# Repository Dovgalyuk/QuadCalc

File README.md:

# QuadCalc
Arduino-based calculator displaying bin/oct/dec/hex versions of argument and result simultaneously

Schematic: https://github.com/Dovgalyuk/QuadCalc/blob/master/pcb-avr/pcb.pdf

## Flashing

Read low fuse bits into file low:

    sudo avrdude -p m2560 -c usbtiny -U lfuse:r:low:r

Write low fuse bits from file low. It should contain single FF byte:

    sudo avrdude -p m2560 -c usbtiny -U lfuse:w:low:r

Write high fuse bits from file high. It should contain single D8 byte:

    sudo avrdude -p m2560 -c usbtiny -U hfuse:w:high:r

Write the firmware image:

    sudo avrdude -p m2560 -c usbtiny -U flash:w:calc.ino.hex:i

# Links

* MK61 hardware emulator: https://gitlab.com/vitasam/mk61s
* E-ink Pi: https://github.com/a8ksh4/paper-pi-handheld
* Handheld Linux Terminal: https://hackaday.io/project/192152-handheld-linux-terminal
* The Forth Deck: http://mynor.org/my4th

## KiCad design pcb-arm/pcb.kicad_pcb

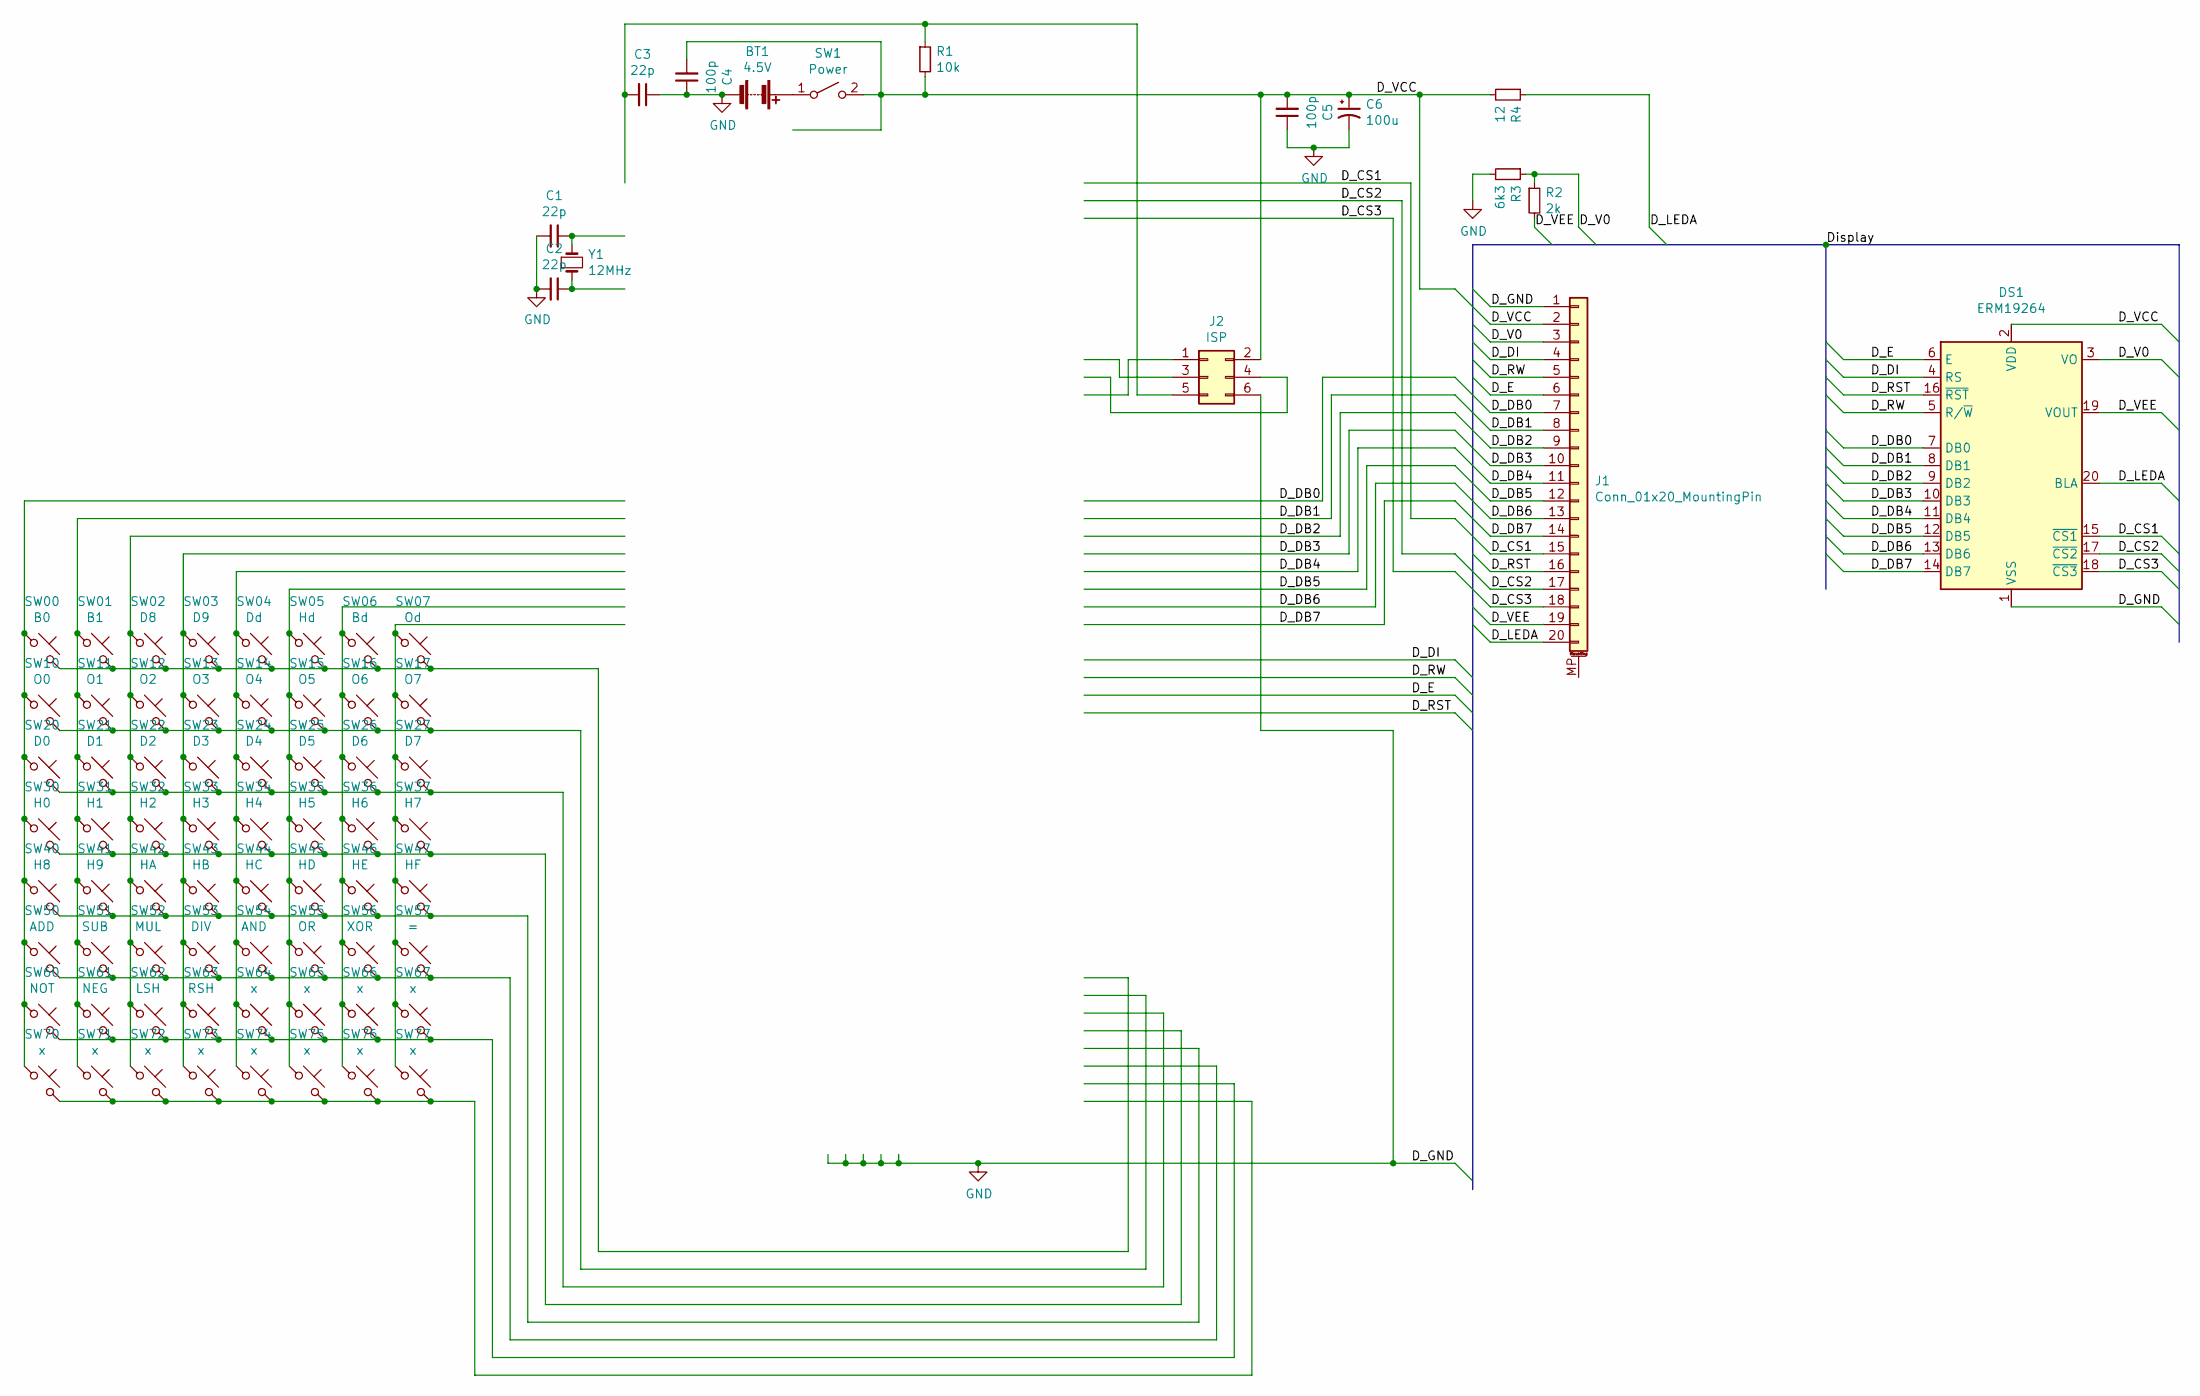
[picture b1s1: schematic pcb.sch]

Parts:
BT1: 4.5V; BatteryHolder_Keystone_2479_3xAAA
C1, C2, C3: 22p; C_0603_1608Metric
C4, C5: 100p; C_0603_1608Metric
C6: 100u; CP_EIA-7343-15_Kemet-W
DS1: ERM19264
J1: Conn_01x20_MountingPin; PinSocket_1x20_P2.54mm_Vertical
J2: ISP; IDC-Header_2x03_P2.54mm_Vertical
R1: 10k; R_0603_1608Metric
R2: 2k; R_0603_1608Metric
R3: 6k3; R_0603_1608Metric
R4: 12; R_0603_1608Metric
SW00: B0; SW_SPST_PTS645
SW01: B1; SW_SPST_PTS645
SW1: Power; SW_CuK_JS202011CQN_DPDT_Straight
SW02: D8; SW_SPST_PTS645
SW03: D9; SW_SPST_PTS645
SW04: Dd; SW_SPST_PTS645
SW05: Hd; SW_SPST_PTS645
SW06: Bd; SW_SPST_PTS645
SW07: Od; SW_SPST_PTS645
SW10: O0; SW_SPST_PTS645
SW11: O1; SW_SPST_PTS645
SW12: O2; SW_SPST_PTS645
SW13: O3; SW_SPST_PTS645
SW14: O4; SW_SPST_PTS645
SW15: O5; SW_SPST_PTS645
SW16: O6; SW_SPST_PTS645
SW17: O7; SW_SPST_PTS645
SW20: D0; SW_SPST_PTS645
SW21: D1; SW_SPST_PTS645
SW22: D2; SW_SPST_PTS645
SW23: D3; SW_SPST_PTS645
SW24: D4; SW_SPST_PTS645
SW25: D5; SW_SPST_PTS645
SW26: D6; SW_SPST_PTS645
SW27: D7; SW_SPST_PTS645
SW30: H0; SW_SPST_PTS645
SW31: H1; SW_SPST_PTS645
SW32: H2; SW_SPST_PTS645
SW33: H3; SW_SPST_PTS645
SW34: H4; SW_SPST_PTS645
SW35: H5; SW_SPST_PTS645
SW36: H6; SW_SPST_PTS645
SW37: H7; SW_SPST_PTS645
SW40: H8; SW_SPST_PTS645
SW41: H9; SW_SPST_PTS645
SW42: HA; SW_SPST_PTS645
SW43: HB; SW_SPST_PTS645
SW44: HC; SW_SPST_PTS645
SW45: HD; SW_SPST_PTS645
SW46: HE; SW_SPST_PTS645
SW47: HF; SW_SPST_PTS645
SW50: ADD; SW_SPST_PTS645
SW51: SUB; SW_SPST_PTS645
SW52: MUL; SW_SPST_PTS645
SW53: DIV; SW_SPST_PTS645
SW54: AND; SW_SPST_PTS645
SW55: OR; SW_SPST_PTS645
SW56: XOR; SW_SPST_PTS645
SW57: =; SW_SPST_PTS645
SW60: NOT; SW_SPST_PTS645
SW61: NEG; SW_SPST_PTS645
SW62: LSH; SW_SPST_PTS645
SW63: RSH; SW_SPST_PTS645
SW64, SW65, SW66, SW67, SW70, SW71, SW72, SW73, SW74, SW75, SW76, SW77: x; SW_SPST_PTS645
Y1: 12MHz; Crystal_SMD_SeikoEpson_MC405-2Pin_9.6x4.1mm_HandSoldering

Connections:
/D_CS1: DS1.15 (~CS1~), J1.15; also elsewhere on the board
/D_CS2: DS1.17 (~CS2~), J1.17; also elsewhere on the board
/D_CS3: DS1.18 (~CS3~), J1.18; also elsewhere on the board
/D_DB0: DS1.7 (DB0), J1.7; also elsewhere on the board
/D_DB1: DS1.8 (DB1), J1.8; also elsewhere on the board
/D_DB2: DS1.9 (DB2), J1.9; also elsewhere on the board
/D_DB3: DS1.10 (DB3), J1.10; also elsewhere on the board
/D_DB4: DS1.11 (DB4), J1.11; also elsewhere on the board
/D_DB5: DS1.12 (DB5), J1.12; also elsewhere on the board
/D_DB6: DS1.13 (DB6), J1.13; also elsewhere on the board
/D_DB7: DS1.14 (DB7), J1.14; also elsewhere on the board
/D_DI: DS1.4 (RS), J1.4; also elsewhere on the board
/D_E: DS1.6 (E), J1.6; also elsewhere on the board
/D_LEDA: DS1.20 (BLA), J1.20, R4.1
/D_RST: DS1.16 (~RST~), J1.16; also elsewhere on the board
/D_RW: DS1.5 (R/~W~), J1.5; also elsewhere on the board
/D_V0: DS1.3 (VO), J1.3, R2.1, R3.1
/D_VCC: C4.2, C5.2, C6.1, DS1.2 (VDD), J1.2, J2.2, R1.2, R4.2, SW1.2 (B); also elsewhere on the board
/D_VEE: DS1.19 (VOUT), J1.19, R2.2
GND: BT1.2 (-), C1.2, C2.2, C3.1, C4.1, C5.1, C6.2, DS1.1 (VSS), J1.1, J2.6, R3.2; also elsewhere on the board
unnamed: BT1.1 (+), SW1.1 (A)
unnamed 21: C1.1, Y1.1; also elsewhere on the board
unnamed 22: C2.1, Y1.2; also elsewhere on the board
unnamed 23: C3.2, J2.5, R1.1; also elsewhere on the board
unnamed 24: J2.1; also elsewhere on the board
unnamed 25: J2.3; also elsewhere on the board
unnamed 26: J2.4; also elsewhere on the board
unnamed 27: SW00.1, SW10.1, SW20.1, SW30.1, SW40.1, SW50.1, SW60.1, SW70.1; also elsewhere on the board
unnamed 28: SW00.2, SW01.2, SW02.2, SW03.2, SW04.2, SW05.2, SW06.2, SW07.2; also elsewhere on the board
unnamed 29: SW01.1, SW11.1, SW21.1, SW31.1, SW41.1, SW51.1, SW61.1, SW71.1; also elsewhere on the board
unnamed 30: SW02.1, SW12.1, SW22.1, SW32.1, SW42.1, SW52.1, SW62.1, SW72.1; also elsewhere on the board
unnamed 31: SW03.1, SW13.1, SW23.1, SW33.1, SW43.1, SW53.1, SW63.1, SW73.1; also elsewhere on the board
unnamed 32: SW04.1, SW14.1, SW24.1, SW34.1, SW44.1, SW54.1, SW64.1, SW74.1; also elsewhere on the board
unnamed 33: SW05.1, SW15.1, SW25.1, SW35.1, SW45.1, SW55.1, SW65.1, SW75.1; also elsewhere on the board
unnamed 34: SW06.1, SW16.1, SW26.1, SW36.1, SW46.1, SW56.1, SW66.1, SW76.1; also elsewhere on the board
unnamed 35: SW07.1, SW17.1, SW27.1, SW37.1, SW47.1, SW57.1, SW67.1, SW77.1; also elsewhere on the board
unnamed 36: SW10.2, SW11.2, SW12.2, SW13.2, SW14.2, SW15.2, SW16.2, SW17.2; also elsewhere on the board
unnamed 37: SW20.2, SW21.2, SW22.2, SW23.2, SW24.2, SW25.2, SW26.2, SW27.2; also elsewhere on the board
unnamed 38: SW30.2, SW31.2, SW32.2, SW33.2, SW34.2, SW35.2, SW36.2, SW37.2; also elsewhere on the board
unnamed 39: SW40.2, SW41.2, SW42.2, SW43.2, SW44.2, SW45.2, SW46.2, SW47.2; also elsewhere on the board
unnamed 40: SW50.2, SW51.2, SW52.2, SW53.2, SW54.2, SW55.2, SW56.2, SW57.2; also elsewhere on the board
unnamed 41: SW60.2, SW61.2, SW62.2, SW63.2, SW64.2, SW65.2, SW66.2, SW67.2; also elsewhere on the board
unnamed 42: SW70.2, SW71.2, SW72.2, SW73.2, SW74.2, SW75.2, SW76.2, SW77.2; also elsewhere on the board

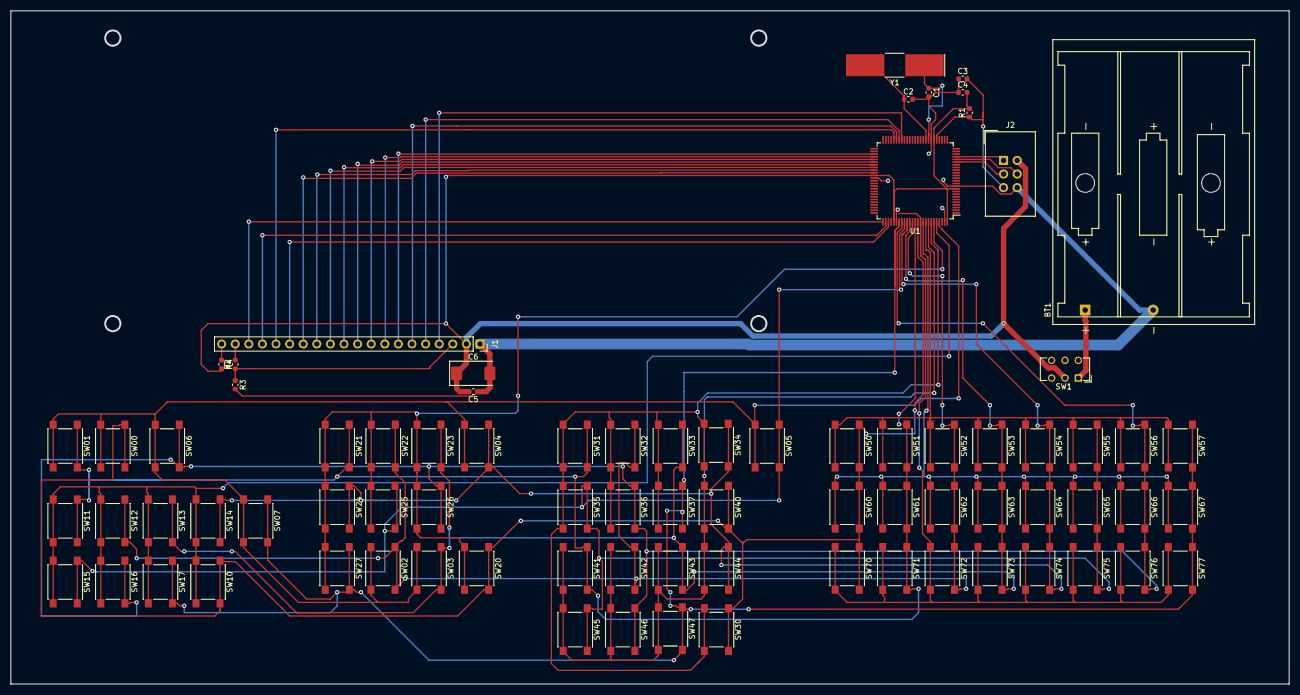
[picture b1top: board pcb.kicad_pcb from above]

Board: 2 copper layers, 238.8 x 125.7 mm, 80 parts (0 on the bottom side), 43 nets.

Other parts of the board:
U1: ATMEGA2560-16AU; TQFP-100_14x14mm_P0.5mm

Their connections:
/D_CS1: U1.78; also elsewhere on the board
/D_CS2: U1.77; also elsewhere on the board
/D_CS3: U1.76; also elsewhere on the board
/D_DB0: U1.53; also elsewhere on the board
/D_DB1: U1.54; also elsewhere on the board
/D_DB2: U1.55; also elsewhere on the board
/D_DB3: U1.56; also elsewhere on the board
/D_DB4: U1.57; also elsewhere on the board
/D_DB5: U1.58; also elsewhere on the board
/D_DB6: U1.59; also elsewhere on the board
/D_DB7: U1.60; also elsewhere on the board
/D_DI: U1.43; also elsewhere on the board
/D_E: U1.45; also elsewhere on the board
/D_RST: U1.46; also elsewhere on the board
/D_RW: U1.44; also elsewhere on the board
/D_VCC: U1.10, U1.31, U1.61, U1.80, U1.100; also elsewhere on the board
GND: U1.11, U1.32, U1.62, U1.81, U1.99; also elsewhere on the board
unnamed 21: U1.33; also elsewhere on the board
unnamed 22: U1.34; also elsewhere on the board
unnamed 23: U1.30; also elsewhere on the board
unnamed 24: U1.22; also elsewhere on the board
unnamed 25: U1.20; also elsewhere on the board
unnamed 26: U1.21; also elsewhere on the board
unnamed 27: U1.89; also elsewhere on the board
unnamed 28: U1.97; also elsewhere on the board
unnamed 29: U1.88; also elsewhere on the board
unnamed 30: U1.87; also elsewhere on the board
unnamed 31: U1.86; also elsewhere on the board
unnamed 32: U1.85; also elsewhere on the board
unnamed 33: U1.84; also elsewhere on the board
unnamed 34: U1.83; also elsewhere on the board
unnamed 35: U1.82; also elsewhere on the board
unnamed 36: U1.96; also elsewhere on the board
unnamed 37: U1.95; also elsewhere on the board
unnamed 38: U1.94; also elsewhere on the board
unnamed 39: U1.93; also elsewhere on the board
unnamed 40: U1.92; also elsewhere on the board
unnamed 41: U1.91; also elsewhere on the board
unnamed 42: U1.90; also elsewhere on the board

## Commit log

2019-08-15 Added first version
2019-08-19 Changed keyboard pins and decimal input
2019-08-30 Added PCB for AVR version
2019-08-30 Added exported schematic
2019-08-30 Added kicad patches with display module
2019-10-23 Added flashing description.
2020-01-22 Updated display layout
2020-09-30 Removed upstreamed kicad stuff
2022-03-04 Readme update
2023-08-02 Added links
